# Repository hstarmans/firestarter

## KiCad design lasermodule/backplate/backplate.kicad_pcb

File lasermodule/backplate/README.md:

# Scanhead Back Plate

Structural rear wall of the laser scanhead enclosure box, providing mechanical rigidity and fastener mounting points.
It supplies current to the laserdiode via two strips to laser module.

## Key Details
* **Role:** Rear structural wall of scanhead enclosure
* **Material:** 1.6mm FR4 PCB material

---
*Part of the [Hexastorm (Firestarter)](../../README.md) open-hardware laser direct imaging project.*

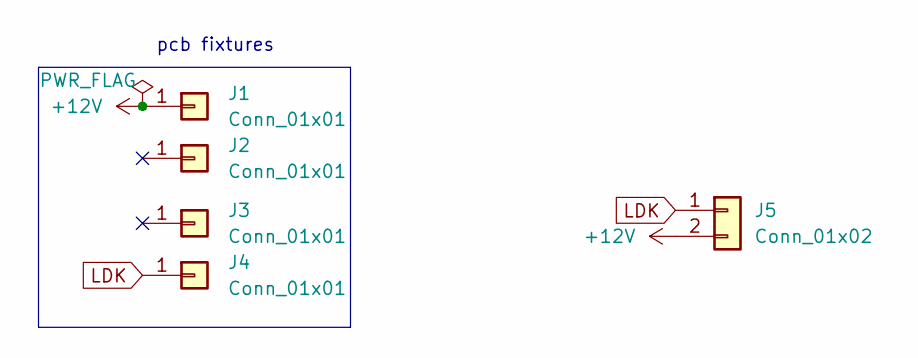
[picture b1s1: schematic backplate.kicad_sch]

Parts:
J1, J2, J3, J4: Conn_01x01; TestPoint_Pad_2.0x2.0mm_nosilk
J5: Conn_01x02; pogopincontact

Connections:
+12V: J1.1 (Pin_1_1), J5.2
LDK: J4.1 (Pin_1_1), J5.1

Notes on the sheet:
pcb fixtures

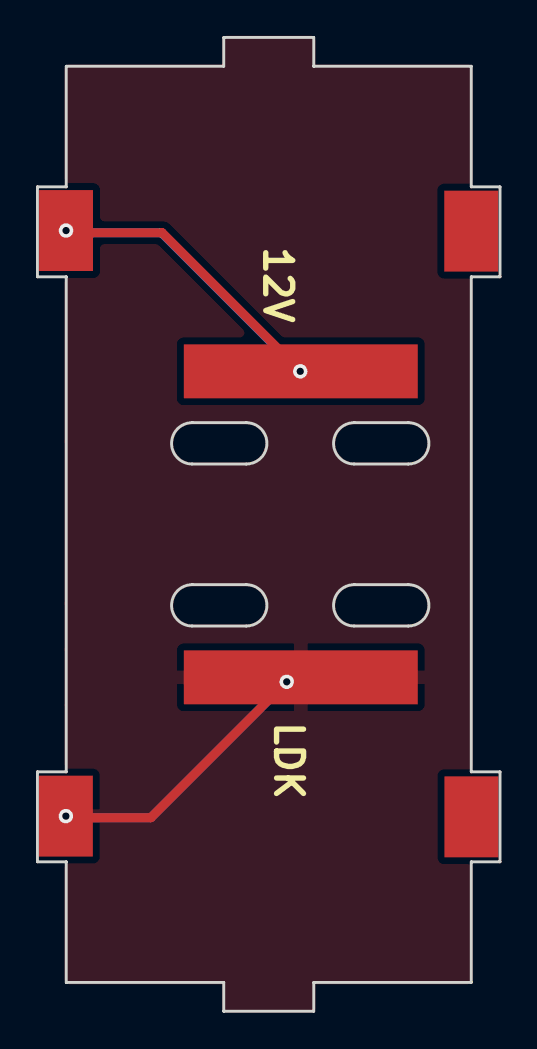
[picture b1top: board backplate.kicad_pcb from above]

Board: 2 copper layers, 25.7 x 54.1 mm, 5 parts (0 on the bottom side), 2 nets.

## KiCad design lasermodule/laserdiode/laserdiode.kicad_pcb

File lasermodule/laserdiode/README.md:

# Laser Diode Mount & Driver PCB

Carrier PCB for the laser diode module inside the scanhead housing. Provides pogo-pin connection to the back plate of the laserhead. Solder contacts provide opton to determine pin routing.

## Key Details

* **Function:** Laser diode mounting and modulation interface
* **Contacts:** Spring-loaded pogo pin pads and direct solder pads for high-speed modulation driver connection
* **Form Factor:** Compact circular/rectangular footprint fitting diode heatsink assembly

---

*Part of the [Hexastorm (Firestarter)](../../README.md) open-hardware laser direct imaging project.*

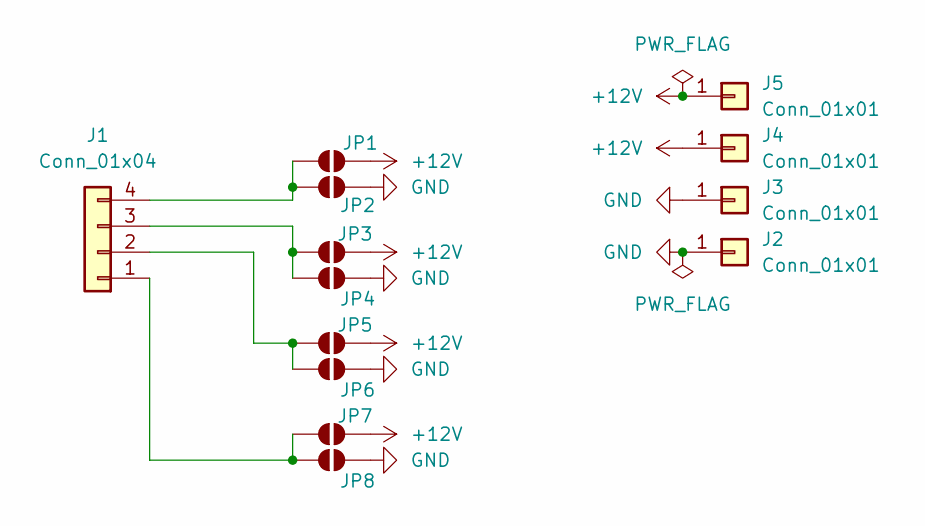
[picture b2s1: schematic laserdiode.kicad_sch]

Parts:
J1: Conn_01x04; TO-18-4
J2, J3, J4: Conn_01x01; 0906115207514110; manuf# 0906-1-15-20-75-14-11-0; Mouser 575-906115
J5: Conn_01x01; 0906115207514110; manuf# 0906-1-15-20-75-14-11-0; mouser# 575-906115
JP1, JP2, JP3, JP4, JP5, JP6, JP7, JP8: SolderJumper_2_Open; SolderJumper-2_P1.3mm_Open_RoundedPad1.0x1.5mm

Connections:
+12V: J4.1 (Pin_1_1), J5.1 (Pin_1_1), JP1.2 (B), JP3.2 (B), JP5.2 (B), JP7.2 (B)
GND: J2.1 (Pin_1_1), J3.1 (Pin_1_1), JP2.2 (B), JP4.2 (B), JP6.2 (B), JP8.2 (B)
unnamed: J1.1, JP7.1 (A), JP8.1 (A)
unnamed: J1.2, JP5.1 (A), JP6.1 (A)
unnamed: J1.3, JP3.1 (A), JP4.1 (A)
unnamed: J1.4, JP1.1 (A), JP2.1 (A)

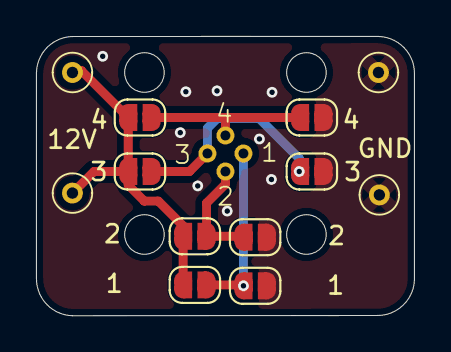
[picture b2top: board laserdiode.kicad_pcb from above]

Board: 2 copper layers, 21.0 x 15.5 mm, 13 parts (1 on the bottom side), 6 nets.
